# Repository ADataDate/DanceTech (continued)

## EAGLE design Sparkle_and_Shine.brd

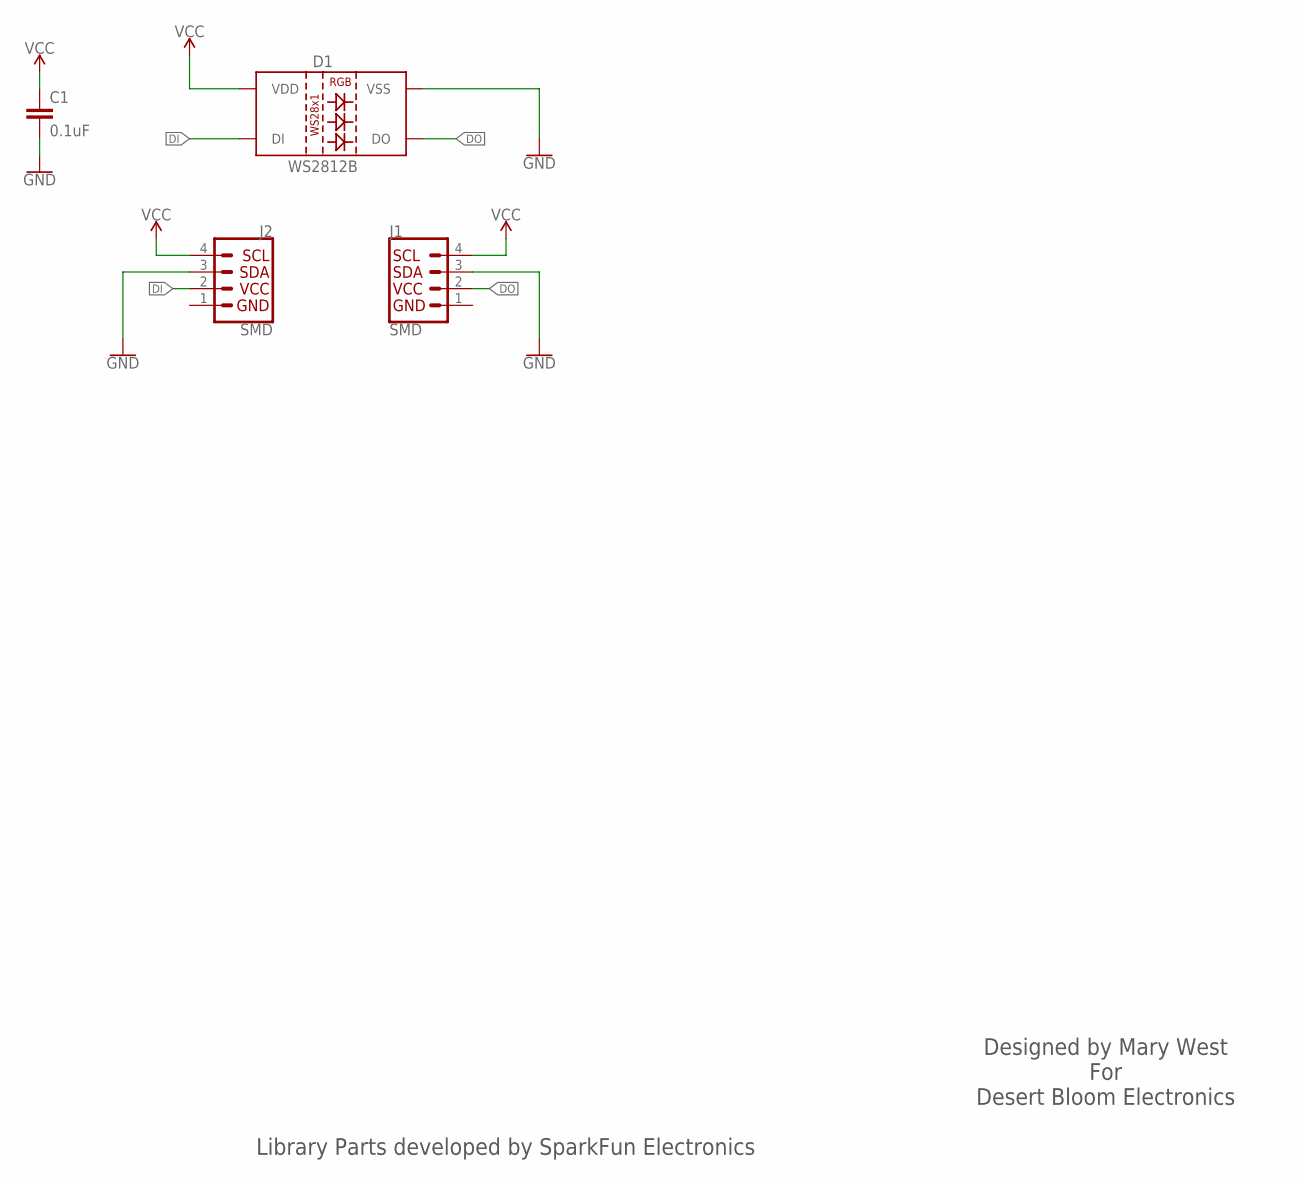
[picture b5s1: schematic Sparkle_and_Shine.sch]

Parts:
C1: 0.1uF; 0603
D1: WS2812B
J1, J2: SMD; 1X04_1MM_RA

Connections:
DI: D1.4 (DI), J2.2 (VCC)
DO: D1.2 (DO), J1.2 (VCC)
GND: C1.2, D1.3 (VSS), J1.1 (GND), J1.3 (SDA), J2.1 (GND), J2.3 (SDA)
VCC: C1.1, D1.1 (VDD), J1.4 (SCL), J2.4 (SCL)

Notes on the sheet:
Designed by Mary West For Desert Bloom Electronics
Library Parts developed by SparkFun Electronics

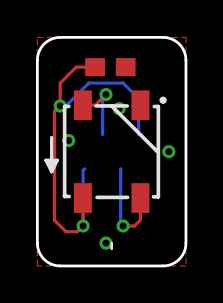
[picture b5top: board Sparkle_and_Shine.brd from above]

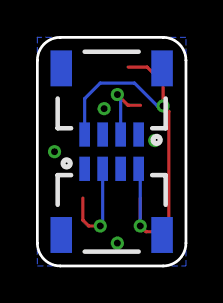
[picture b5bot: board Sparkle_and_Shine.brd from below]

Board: 2 copper layers, 8.3 x 12.7 mm, 4 parts (2 on the bottom side), 4 nets.

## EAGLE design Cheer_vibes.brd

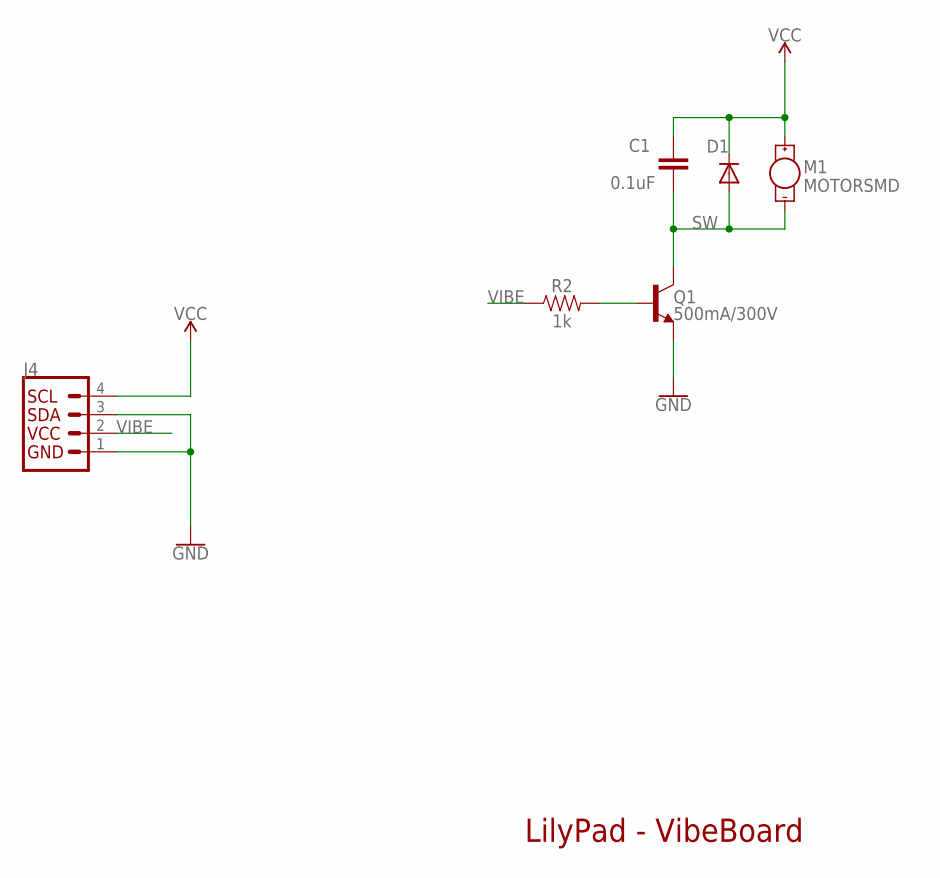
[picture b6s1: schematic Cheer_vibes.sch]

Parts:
C1: 0.1uF; 0603
D1: DIODESOD; SOD-323
J4: QWIIC_CONNECTORJS-1MM; 1X04_1MM_RA
M1: MOTORSMD; VIBE-MOTOR-10MM-SMD
Q1: 500mA/300V; SOT23-3
R2: 1k; 0603

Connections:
GND: J4.1 (GND), J4.3 (SDA), Q1.2 (E)
unnamed: Q1.1 (B), R2.2
SW: C1.2, D1.2 (A), M1.P$2 (-), Q1.3 (C)
VCC: C1.1, D1.1 (C), J4.4 (SCL), M1.P$1 (+)
VIBE: J4.2 (VCC), R2.1

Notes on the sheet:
LilyPad - VibeBoard

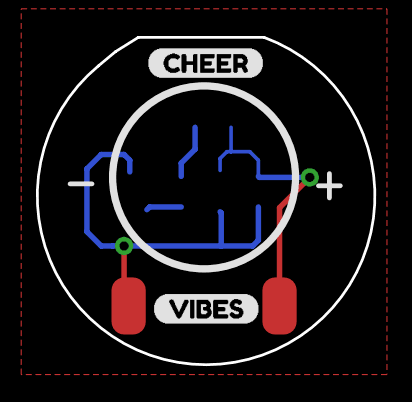
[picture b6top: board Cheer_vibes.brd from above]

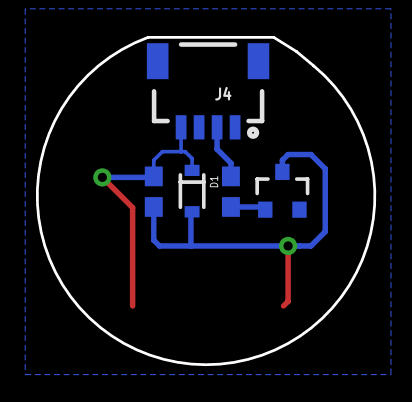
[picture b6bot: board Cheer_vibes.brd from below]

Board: 2 copper layers, 18.7 x 18.2 mm, 8 parts (5 on the bottom side), 5 nets.

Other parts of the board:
U$1: CHEER0
U$2: VIBES1

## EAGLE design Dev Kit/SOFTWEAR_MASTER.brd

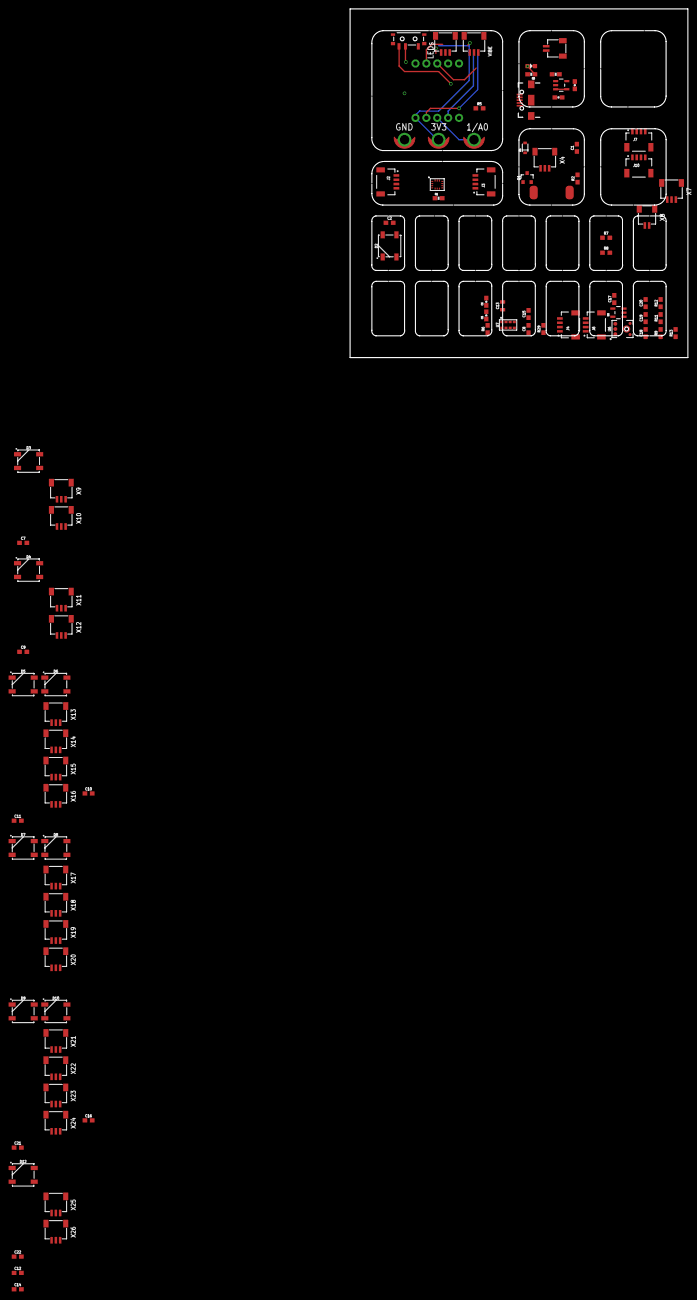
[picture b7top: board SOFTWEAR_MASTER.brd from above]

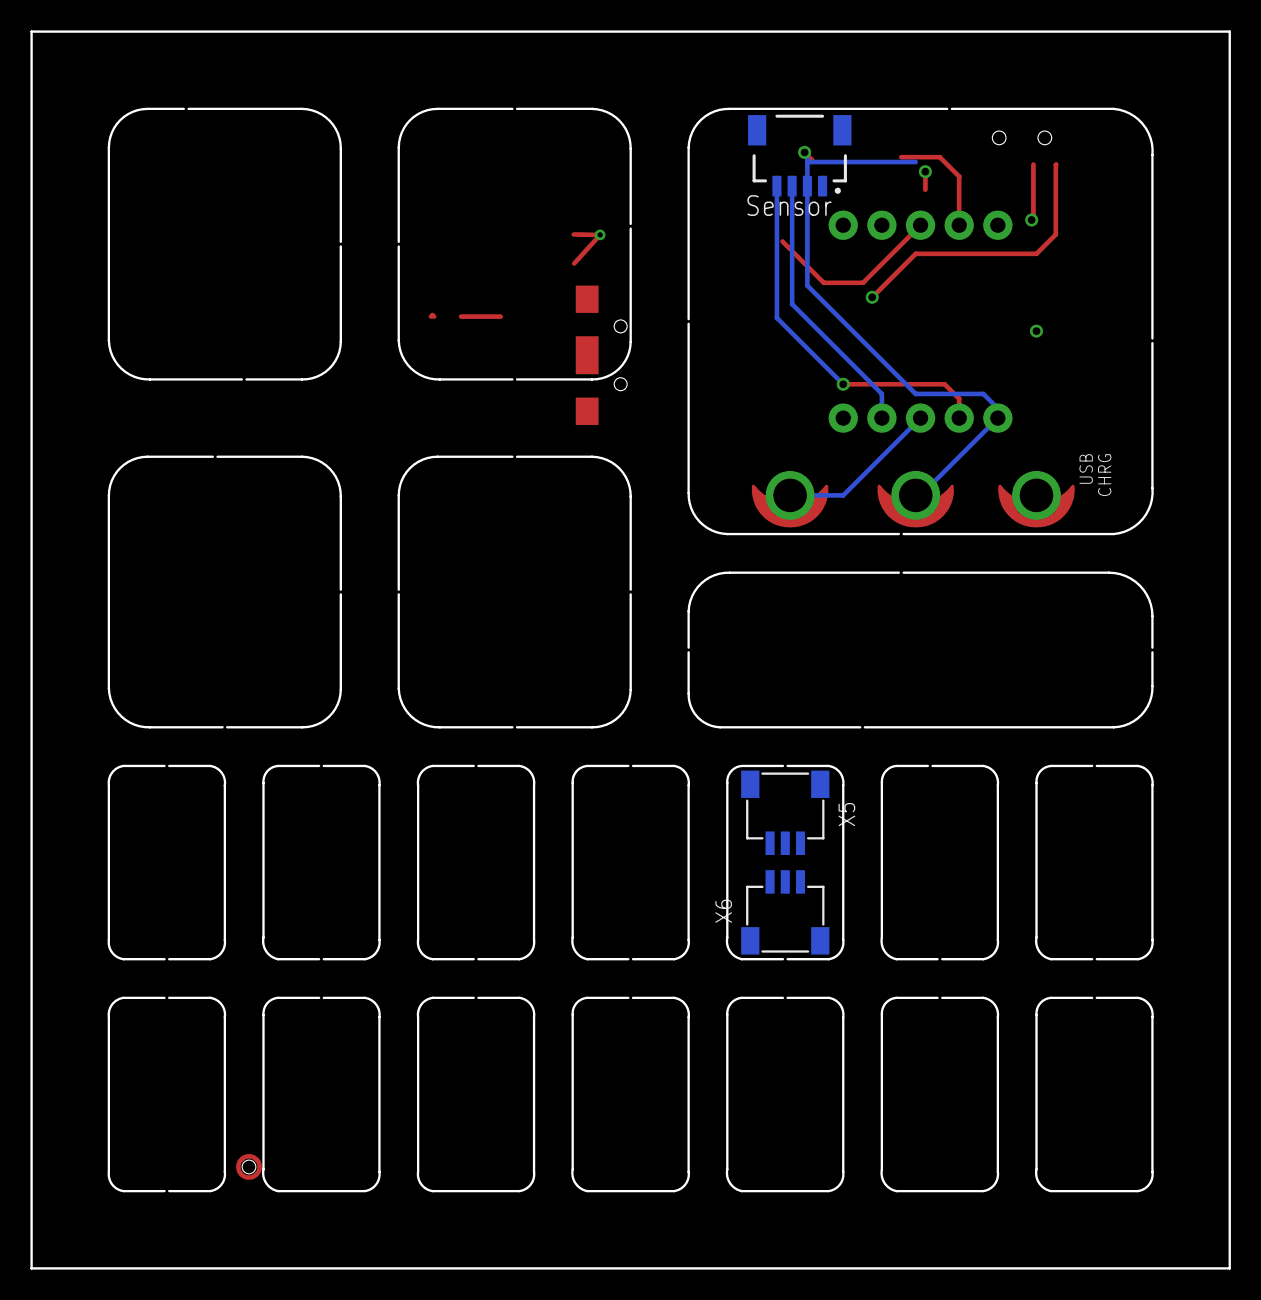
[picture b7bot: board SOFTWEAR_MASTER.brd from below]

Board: 2 copper layers, 78.7 x 81.3 mm, 100 parts (3 on the bottom side), 28 nets.

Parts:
C1, C2, C7, C8, C9, C10, C11, C12, C14, C16, C18, C21, C22: 0.1uF; 0603
C3, C4: 4.7uF; 0603-CAP
C5, C6: 0.1uF; 0603-CAP
C13: 10uF; 0805
C15, C20: 1.0uF; 0603
C17: 100pF; 0603
C19: 4.7uF; 0603
D1: SOD-323
D2, D3, D4, D5, D6, D7, D8, D9, D10, D12: WS2812B
D11: RED; LED-0603
FRAME1, FRAME2, FRAME3, FRAME4, FRAME5, FRAME6: FRAME-LETTERNO_PACKAGE; DUMMY
J1, J5, J8: SEWTAP_SMALL; PETAL-SMALL
J2, J3, J4, J6, J7, J9, J10: QWIIC_RIGHT_ANGLE; JST04_1MM_RA
JP3, JP4: 1X05_ROUND_76
JP9: Micro USB; USB-AB-MICRO-SMD_V03
M1: MOTORSMD; VIBE-MOTOR-10MM-SMD
Q1: 500mA/300V; SOT23-3
R1: 10K; 0603-RES
R2: 1k; 0603
R3: 330; 0603-RES
R4: 2.0k; 0603-RES
R5, R6, R7, R8: 4.7k; 0603
R9, R11: 10k; 0603
R12: 1.5k; 0603
R13: 100k; 0603
R29: 0; 0603
S1: SWITCH_SPST_SMD_A
U1: MCP73831; SOT23-5
U2: LSM6DS3; LGA14L_DOT_INDICATOR
U5: OPA344; SOT23-5
U6: ADMP401
U7: APDS-9960
X1, X8: SM02B-SRSS-TB
X2, X3, X4, X5, X6, X7, X9, X10, X11, X12, X13, X14, X15, X16, X17, X18, X19, X20, X21, X22, X23, X24, X25, X26: SM03B-SRSS-TB

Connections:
1: J7.4, J10.4
2: J7.3, J10.3
3: X3.1, X7.1
3.3V: C1.1, C2.1, C5.1, C6.1, C7.1, C8.1, C9.1, C10.1, C11.1, C12.1, C14.1, C15.1, C16.1, C18.2, C21.1, C22.1, D1.1, D2.1, D3.1, D4.1, D5.1, D6.1, D7.1, D8.1, D9.1, D10.1, D12.1, J2.2, J3.2, J4.2, J5.1, J6.2, J7.2, J9.2, J10.2, JP4.1, M1.P$1, R1.2, R5.2, R6.2, R7.2, R8.2, R9.2, R29.2, U2.5, U2.8, U5.5, U6.5, U7.8, X2.3, X3.3, X4.3, X5.3, X6.3, X7.3, X9.3, X10.3, X11.3, X12.3, X13.3, X14.3, X15.3, X16.3, X17.3, X18.3, X19.3, X20.3, X21.3, X22.3, X23.3, X24.3, X25.3, X26.3
A3: C17.2, R13.1, U5.1
CS: R1.1, U2.12
D1_A0_PA02: J1.1, JP4.3
DI: D2.4, D3.4, D4.4, D5.4, D6.4, D7.4, D8.4, D9.4, D10.4, D12.4, X5.1, X9.1, X11.1, X13.1, X15.1, X17.1, X19.1, X21.1, X23.1, X25.1
DO: D2.2, D3.2, D4.2, D5.2, D6.2, D7.2, D8.2, D9.2, D10.2, D12.2, X6.1, X10.1, X12.1, X14.1, X16.1, X18.1, X20.1, X22.1, X24.1, X26.1
GND: C2.2, C3.2, C4.2, C5.2, C6.2, C7.2, C8.2, C9.2, C10.2, C11.2, C12.2, C13.2, C14.2, C15.2, C16.2, C18.1, C20.2, C21.2, C22.2, D2.3, D3.3, D4.3, D5.3, D6.3, D7.3, D8.3, D9.3, D10.3, D12.3, J2.1, J3.1, J4.1, J6.1, J7.1, J8.1, J9.1, J10.1, JP3.2, JP9.GND1, Q1.2, R4.2, R11.1, U1.2, U2.1, U2.2, U2.3, U2.6, U2.7, U5.2, U6.2, U6.4, U6.6, U7.6, X1.1, X2.2, X3.2, X4.2, X5.2, X6.2, X7.2, X8.1, X9.2, X10.2, X11.2, X12.2, X13.2, X14.2, X15.2, X16.2, X17.2, X18.2, X19.2, X20.2, X21.2, X22.2, X23.2, X24.2, X25.2, X26.2
LEDA: C13.1, R29.1, U7.5
unnamed: C19.1, U6.1
unnamed: Q1.1, R2.2
unnamed: D11.A, R3.1
unnamed: U7.3, U7.4
unnamed: C17.1, R12.1, R13.2, U5.4
unnamed: C19.2, R12.2
unnamed: C20.1, R9.1, R11.2, U5.3
NEO: JP3.4, X2.1
PROG: R4.1, U1.5
SCL: J2.4, J3.4, J4.4, J6.4, J9.4, JP4.2, R6.1, R8.1, U2.13, U7.7
SDA: J2.3, J3.3, J4.3, J6.3, J9.3, JP4.4, R5.1, R7.1, U2.14, U7.1
STAT: D11.C, U1.1
SW: C1.2, D1.2, M1.P$2, Q1.3
VBAT: JP3.1, S1.1, X8.2
VBAT_OUT: C4.1, S1.2, U1.3, X1.2
VIBE: JP3.3, R2.1, X4.1
VUSB: C3.1, JP9.VBUS1, R3.2, U1.4

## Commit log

2020-06-12 adding LED breakout, Trinket breakout, haptic motor breakout, & WIP dev kit
2020-06-12 Updating silk on vibe board
2020-10-30 Updates to files and WIP on Dev Kit
2020-12-21 adding microbit files
2020-12-27 updated design
2021-01-04 updated silk
2021-01-04 added cap touch BOB
